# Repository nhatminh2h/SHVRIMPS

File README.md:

# SHVRIMPS: Synchronised High-Voltage aRbItrary Modular Power Supply

SHVRIMPS is a high-voltage generator and optical imaging setup, capable of
- Outputting arbitrary high-voltage waveforms with an amplitude of 15 kV and a rise time less than 10 ms for load resistances below 8 MΩ.
- Eight independent synchronous and asynchronous 16-bit output channels.
- Monitoring the output high voltages and currents at adjustable sampling rate. Maximum rate of 9875 samples per second.
- Recording video of samples at a rate of 120 fps at 640x480 pixels.
- Displaying live video feed, control panel, and monitoring data on a GUI, accessible over Ethernet.

It consists of three main components: 1) an imaging system based on a Raspberry Pi 4B with a camera, producing a live video stream 2) a DAQ board compatible with either Arduino Nano 33 BLE or ESP32 DevKitC, and c) a multi-channel arbitrary waveform HV supply.

The repository is structured as follows:
- demonstration: videos and matlab figures
- diagrams: block diagrams of the entire setup and individual components
- hardware: KiCAD files showing the PCB design files
- setup: setup files
- software: source files for the Pi and DAQ board

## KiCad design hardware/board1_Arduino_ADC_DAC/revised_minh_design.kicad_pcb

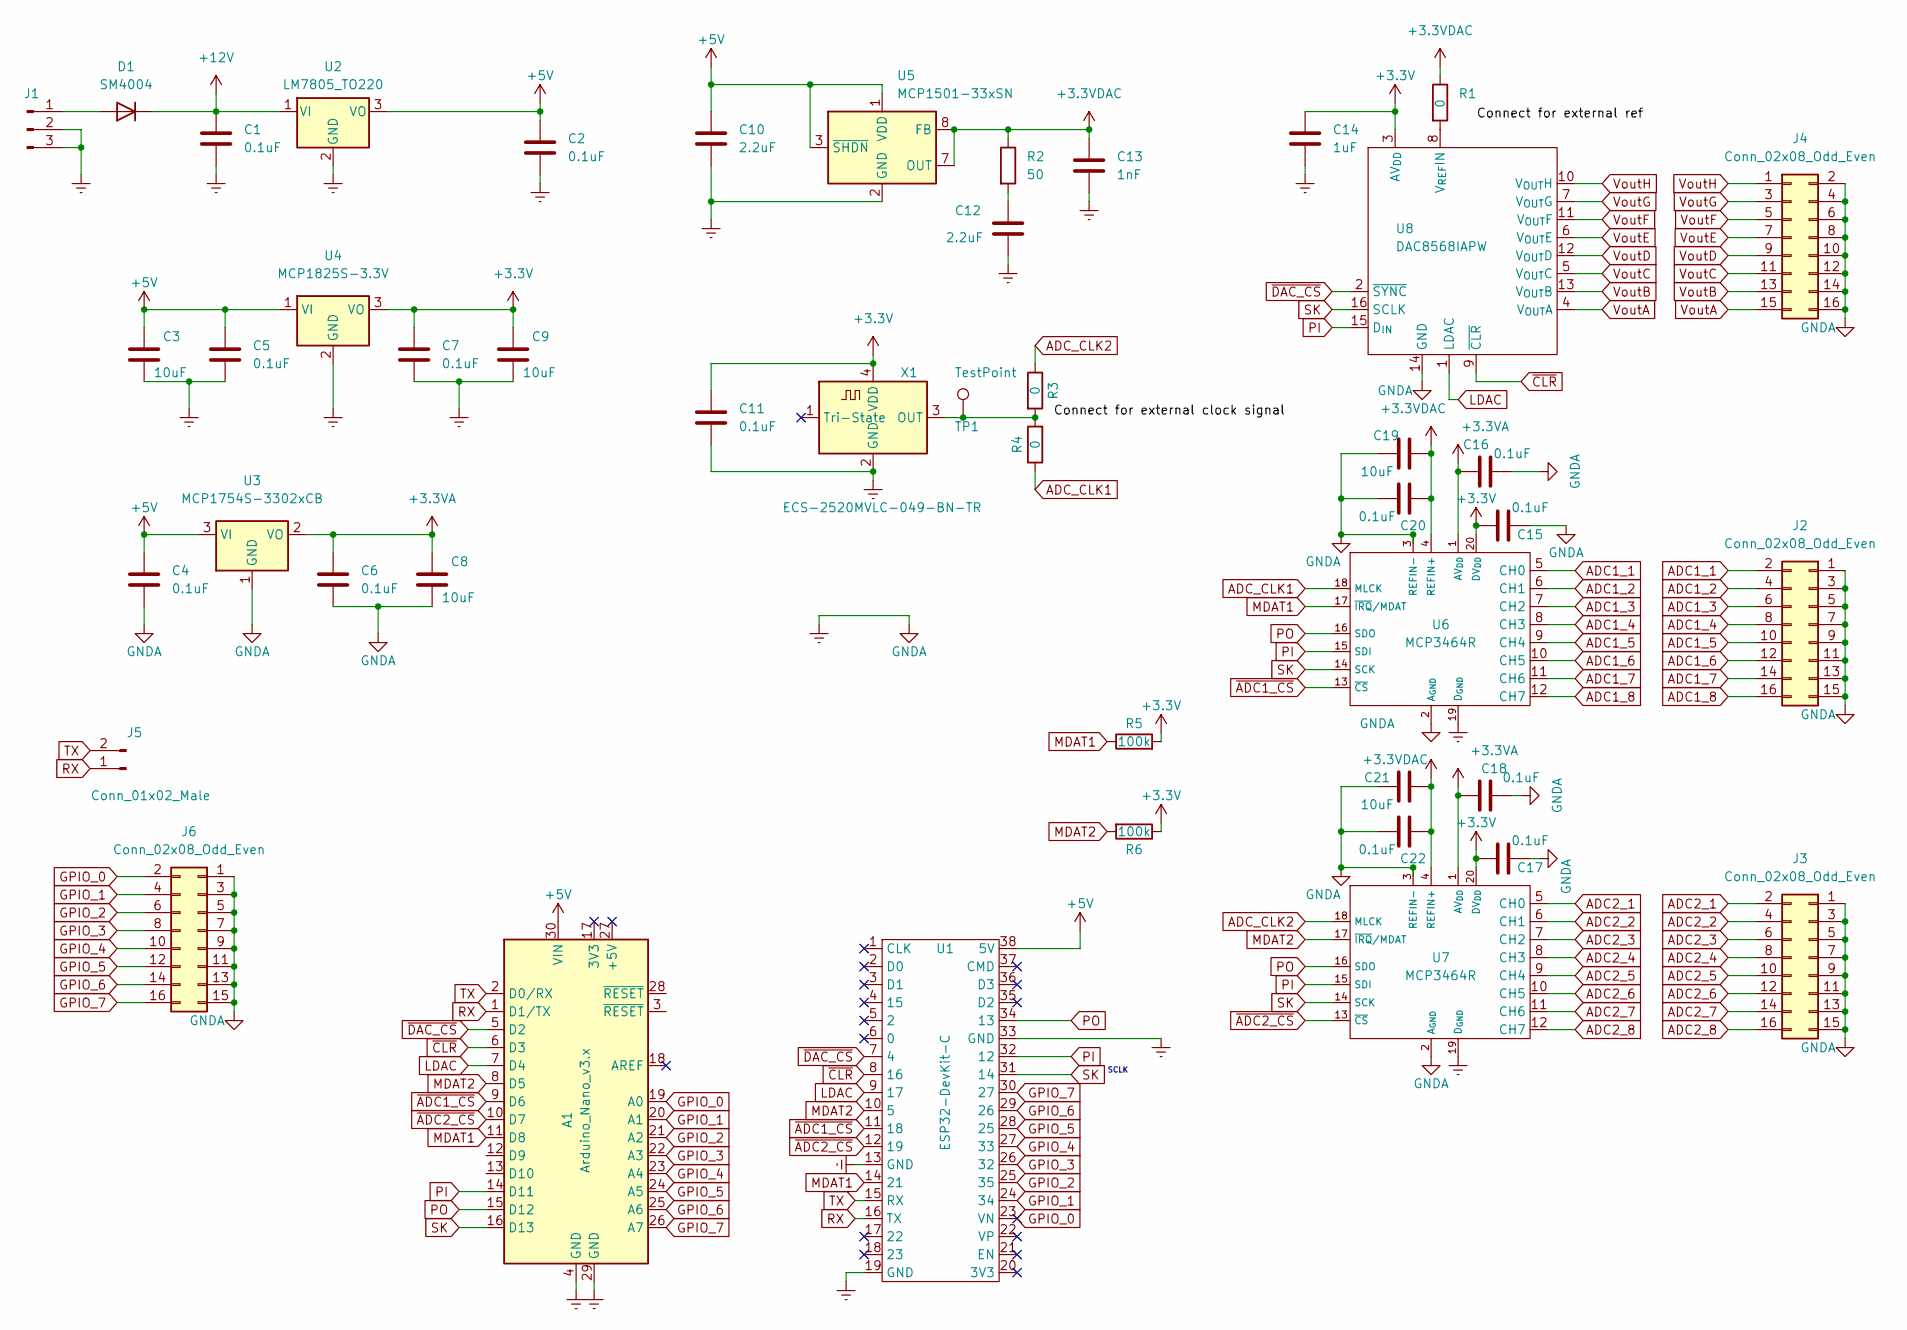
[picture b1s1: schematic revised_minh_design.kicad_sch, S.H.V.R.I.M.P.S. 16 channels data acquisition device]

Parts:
A1: Arduino_Nano_v3.x; Arduino_Nano
C1, C2, C4, C5, C6, C7, C11, C15, C16, C17, C18, C20, C22: 0.1uF; C_0805_2012Metric_Pad1.18x1.45mm_HandSolder
C3, C8, C9, C19, C21: 10uF; C_0805_2012Metric_Pad1.18x1.45mm_HandSolder
C10, C12: 2.2uF; C_0805_2012Metric_Pad1.18x1.45mm_HandSolder
C13: 1nF; C_0805_2012Metric_Pad1.18x1.45mm_HandSolder
C14: 1uF; C_0805_2012Metric_Pad1.18x1.45mm_HandSolder
D1: SM4004; D_MELF
J1: Conn_01x03_Male; PinSocket_1x03_P2.54mm_Vertical
J2, J3, J4, J6: Conn_02x08_Odd_Even; PinSocket_2x08_P2.54mm_Vertical
J5: Conn_01x02_Male; PinSocket_1x02_P2.54mm_Vertical
R1, R3, R4: 0; R_0805_2012Metric_Pad1.20x1.40mm_HandSolder
R2: 50; R_0805_2012Metric_Pad1.20x1.40mm_HandSolder
R5, R6: 100k; R_0805_2012Metric_Pad1.20x1.40mm_HandSolder
TP1: TestPoint; PinHeader_1x01_P2.54mm_Vertical
U1: ESP32-DevKit-C; ESP32-devkitC-v4
U2: LM7805_TO220; TO-220-3_Vertical
U3: MCP1754S-3302xCB; SOT-23
U4: MCP1825S-3.3V; SOT-223-3_TabPin2
U5: MCP1501-33xSN; SOIC-8_3.9x4.9mm_P1.27mm
U6, U7: MCP3464R; TSSOP-20_4.4x6.5mm_P0.65mm
U8: DAC8568IAPW; TSSOP-16-1EP_4.4x5mm_P0.65mm
X1: ECS-2520MVLC-049-BN-TR; Oscillator_SMD_ECS_2520MV-xxx-xx-4Pin_2.5x2.0mm

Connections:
+3.3VA: C6.1, C8.1, C16.1, C18.1, U3.2 (VO), U6.1 (AV_{DD}), U7.1 (AV_{DD})
+3.3VDAC: C13.1, C19.1, C20.1, C21.1, C22.1, R1.1, R2.1, U5.7 (OUT), U5.8 (FB), U6.4 (REFIN+), U7.4 (REFIN+)
+3V3: C7.1, C9.1, C11.1, C14.1, C15.1, C17.1, R5.2, R6.1, U4.3 (VO), U6.20 (DV_{DD}), U7.20 (DV_{DD}), U8.3 (AV_{DD}), X1.4 (VDD)
+5V: A1.30 (VIN), C2.1, C3.1, C4.1, C5.1, C10.1, U1.38 (5V), U2.3 (VO), U3.3 (VI), U4.1 (VI), U5.1 (VDD), U5.3 (~SHDN)
+12V: C1.1, D1.1 (K), U2.1 (VI)
ADC1_1: J2.2, U6.5 (CH0)
ADC1_2: J2.4, U6.6 (CH1)
ADC1_3: J2.6, U6.7 (CH2)
ADC1_4: J2.8, U6.8 (CH3)
ADC1_5: J2.10, U6.9 (CH4)
ADC1_6: J2.12, U6.10 (CH5)
ADC1_7: J2.14, U6.11 (CH6)
ADC1_8: J2.16, U6.12 (CH7)
ADC2_1: J3.2, U7.5 (CH0)
ADC2_2: J3.4, U7.6 (CH1)
ADC2_3: J3.6, U7.7 (CH2)
ADC2_4: J3.8, U7.8 (CH3)
ADC2_5: J3.10, U7.9 (CH4)
ADC2_6: J3.12, U7.10 (CH5)
ADC2_7: J3.14, U7.11 (CH6)
ADC2_8: J3.16, U7.12 (CH7)
ADC_CLK1: R4.1, U6.18 (MLCK)
ADC_CLK2: R3.1, U7.18 (MLCK)
Earth: A1.4 (GND), A1.29 (GND), C1.2, C2.2, C3.2, C4.2, C5.2, C6.2, C7.2, C8.2, C9.2, C10.2, C11.2, C12.2, C13.2, C14.2, C15.2, C16.2, C17.2, C18.2, C19.2, C20.2, C21.2, C22.2, J1.2, J1.3, J2.1, J2.3, J2.5, J2.7, J2.9, J2.11, J2.13, J2.15, J3.1, J3.3, J3.5, J3.7, J3.9, J3.11, J3.13, J3.15, J4.2, J4.4, J4.6, J4.8, J4.10, J4.12, J4.14, J4.16, J6.1, J6.3, J6.5, J6.7, J6.9, J6.11, J6.13, J6.15, U1.13 (GND), U1.19 (GND), U1.33 (GND), U2.2 (GND), U3.1 (GND), U4.2 (GND), U5.2 (GND), U5.4 (GND), U5.5 (GND), U5.6 (GND), U6.2 (A_{GND}), U6.3 (REFIN-), U6.19 (D_{GND}), U7.2 (A_{GND}), U7.3 (REFIN-), U7.19 (D_{GND}), U8.14 (GND), X1.2 (GND)
GPIO_0: A1.19 (A0), J6.2, U1.23 (VN)
GPIO_1: A1.20 (A1), J6.4, U1.24 (34)
GPIO_2: A1.21 (A2), J6.6, U1.25 (35)
GPIO_3: A1.22 (A3), J6.8, U1.26 (32)
GPIO_4: A1.23 (A4), J6.10, U1.27 (33)
GPIO_5: A1.24 (A5), J6.12, U1.28 (25)
GPIO_6: A1.25 (A6), J6.14, U1.29 (26)
GPIO_7: A1.26 (A7), J6.16, U1.30 (27)
LDAC: A1.7 (D4), U1.9 (17), U8.1 (LDAC)
MDAT1: A1.11 (D8), R5.1, U1.14 (21), U6.17 (~IRQ/MDAT)
MDAT2: A1.8 (D5), R6.2, U1.10 (5), U7.17 (~IRQ/MDAT)
unnamed: C12.1, R2.2
unnamed: D1.2 (A), J1.1
unnamed: R1.2, U8.8 (V_{REF}IN)
unnamed: R3.2, R4.2, TP1.1, X1.3 (OUT)
PI: A1.14 (D11), U1.32 (12), U6.15 (SDI), U7.15 (SDI), U8.15 (D_{IN})
PO: A1.15 (D12), U1.34 (13), U6.16 (SDO), U7.16 (SDO)
RX: A1.1 (D1/TX), J5.1, U1.16 (TX)
SK: A1.16 (D13), U1.31 (14), U6.14 (SCK), U7.14 (SCK), U8.16 (SCLK)
TX: A1.2 (D0/RX), J5.2, U1.15 (RX)
VoutA: J4.15, U8.4 (V_{OUT}A)
VoutB: J4.13, U8.13 (V_{OUT}B)
VoutC: J4.11, U8.5 (V_{OUT}C)
VoutD: J4.9, U8.12 (V_{OUT}D)
VoutE: J4.7, U8.6 (V_{OUT}E)
VoutF: J4.5, U8.11 (V_{OUT}F)
VoutG: J4.3, U8.7 (V_{OUT}G)
VoutH: J4.1, U8.10 (V_{OUT}H)
~ADC1_CS: A1.9 (D6), U1.11 (18), U6.13 (~CS)
~ADC2_CS: A1.10 (D7), U1.12 (19), U7.13 (~CS)
~CLR: A1.6 (D3), U1.8 (16), U8.9 (~CLR)
~DAC_CS: A1.5 (D2), U1.7 (4), U8.2 (~SYNC)

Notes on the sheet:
SCLK

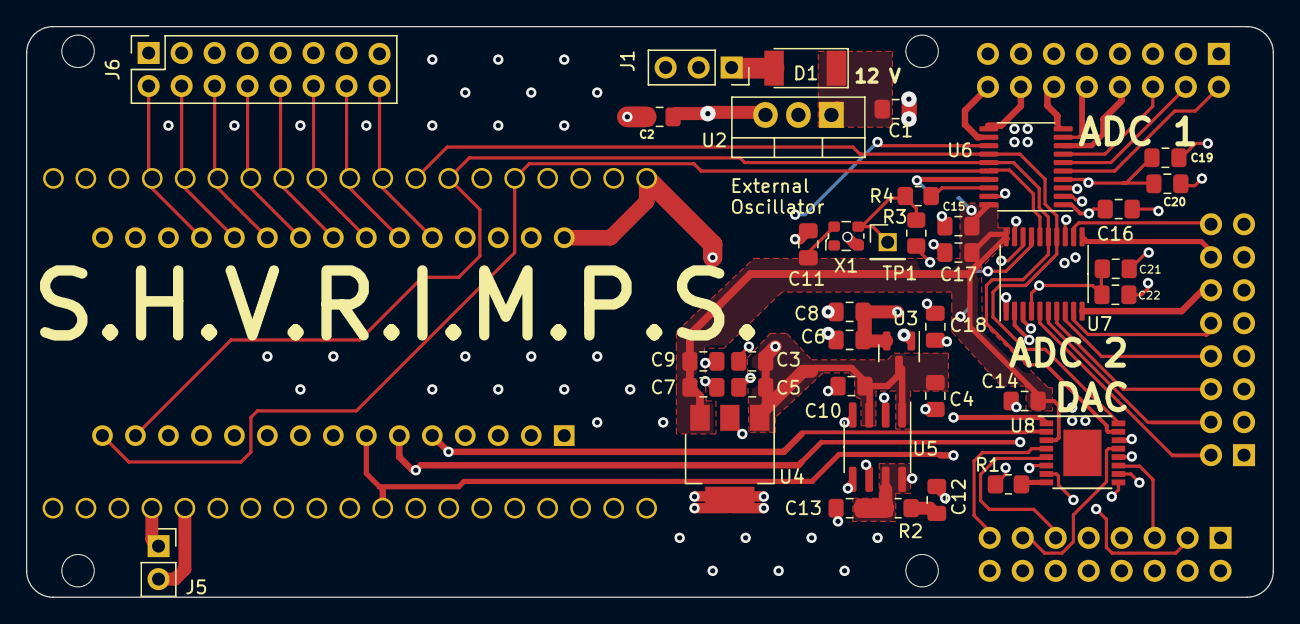
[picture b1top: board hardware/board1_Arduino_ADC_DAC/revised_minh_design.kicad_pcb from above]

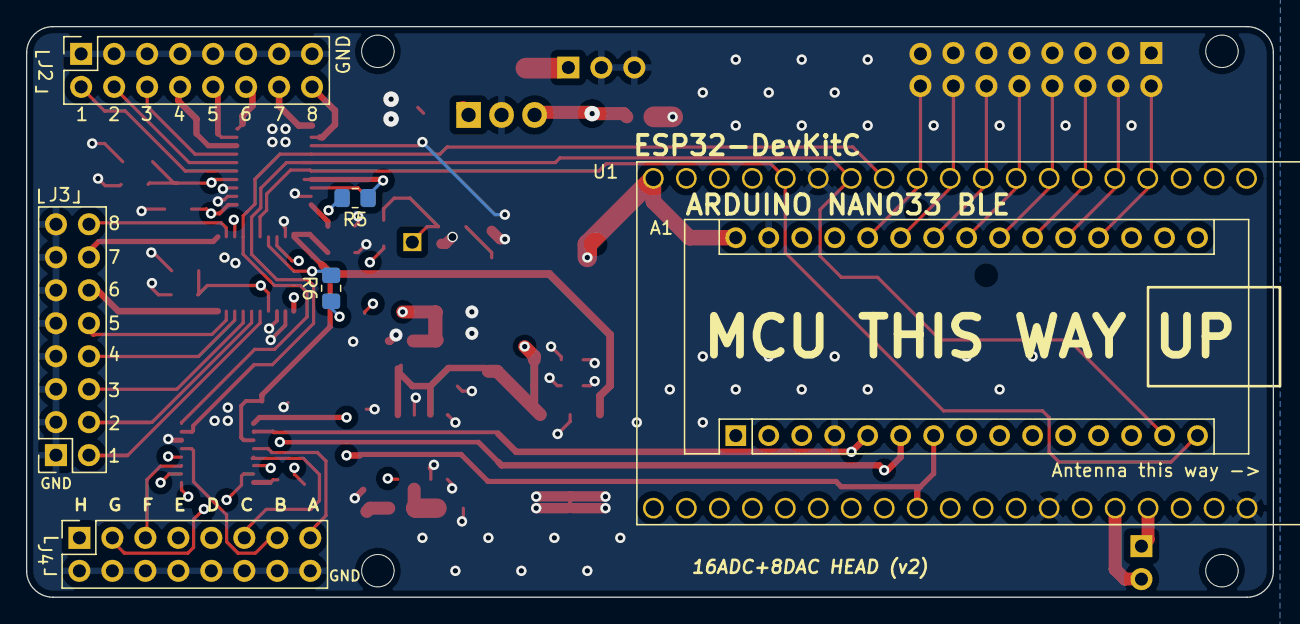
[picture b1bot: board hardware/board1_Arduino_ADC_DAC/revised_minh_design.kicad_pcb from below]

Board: 4 copper layers, 96.0 x 43.9 mm, 50 parts (7 on the bottom side), 56 nets.

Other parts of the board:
 : MountingHole_2.5mm
 #2,  #3,  #4: MountingHole_2.5mm

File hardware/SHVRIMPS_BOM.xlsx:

Ref | Qnty | Value | Description | Vendor | Manufacture number | Alternative Option | Unit Price | Total Price
A1, | 1 | Arduino_Nano_v3.x | Arduino Nano 33 BLE | https://uk.rs-online.com/web/p/arduino/1927587 | ABX00030 |  | 25.86 | 25.86
C1, C2, C4, C5, C6, C7, C11, C15, C16, C17, C18, C20, C22, | 13 | 0.1uF | Capacitor_SMD_0805 | https://www.mouser.co.uk/ProductDetail/Vishay-Vitramon/VJ080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 | VJ0805Y104JXAMR | SMD components of same value | 0.34399999999999997 | 4.4719999999999995
C3, C8, C9, C19, C21, | 5 | 10uF | Capacitor_SMD_0806 | https://www.mouser.co.uk/ProductDetail/KYOCERA-AVX/0805ZD106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 | 0805ZD106KAT2A | SMD components of same value | 0.17599999999999999 | 0.87999999999999989
C10, C12, | 2 | 2.2uF | Capacitor_SMD_0807 | https://www.mouser.co.uk/ProductDetail/KEMET/C0805C225K3RACA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 |  | SMD components of same value | 0.24399999999999999 | 0.48799999999999999
C13, | 1 | 1nF | Capacitor_SMD_0808 | https://www.mouser.co.uk/ProductDetail/KYOCERA-AVX/08055A102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 |  | SMD components of same value | 0.109 | 0.109
C14, | 1 | 1uF | Capacitor_SMD_0809 | https://www.mouser.co.uk/ProductDetail/KYOCERA-AVX/0805DC105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 |  | SMD components of same value | 0.185 | 0.185
D1, | 1 | SM4004 | 400V 1A General Purpose Rectifier Diode, MELF | https://eu.mouser.com/ProductDetail/Rectron/FM4004-W?qs=Iw9U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 | FM4004-W | SMD components of same value | 0.254 | 0.254
J1, | 1 | Conn_01x03_Male | Single row, 01x03, 2.54mm pitch | https://www.mouser.co.uk/ProductDetail/Molex/90136-1303?qs=k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 | 90136-1303 | 2.54mm pitch connectors | 1.45 | 1.45
 | 1 | Conn_01x03_Female | Receptacle | https://www.mouser.co.uk/ProductDetail/Molex/90156-0143?qs=j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 | 90156-0143 | 2.54mm pitch connectors | 0.53800000000000003 | 0.53800000000000003
J2, J3, J4, | 3 | Conn_02x08_Male | Double row, 02x08, 2.54mm pitch | https://www.mouser.co.uk/ProductDetail/Molex/90130-1316?qs=p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 | 90130-1316 | 2.54mm pitch connectors | 4.29 | 12.870000000000001
 | 3 | Conn_02x08_Female |  | https://www.mouser.co.uk/ProductDetail/Molex/90142-0016?qs=k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 | 90142-0016 | 2.54mm pitch connectors | 1.24 | 3.7199999999999998
J5, | 1 | Conn_01x02_Male | Single row, 01x02, 2.54mm pitch | https://www.mouser.co.uk/ProductDetail/Molex/90136-1202?qs=z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 | 90136-1202 | 2.54mm pitch connectors | 1.1399999999999999 | 1.1399999999999999
 | 1 | Conn_01x02_Female |  | https://www.mouser.co.uk/ProductDetail/Molex/90156-0142?qs=j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 | 90156-0142 | 2.54mm pitch connectors | 0.38600000000000001 | 0.38600000000000001
R1, R3, R4, | 3 | 0 Ohm | Resistor_SMD_0803 | https://www.mouser.co.uk/ProductDetail/Vishay-Dale/CRCW08050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 | CRCW08050000Z0EAC | SMD components of same value | 8.4000000000000005E-2 | 0.252
R2, | 1 | 50 Ohm | Resistor_SMD_0804 | https://uk.farnell.com/panasonic/era6aeb49r9v/res-0805-49r9-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 | ERA6AEB49R9V | SMD components of same value | 0.253 | 0.253
R5, R6, | 2 | 100k Ohm | Resistor_SMD_0805 | https://www.mouser.co.uk/ProductDetail/Vishay-Dale/RCS080510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 |  | SMD components of same value | 0.20200000000000001 | 0.40400000000000003
U1, | 1 | ESP32-DevKit-C | Alternative microcontroller: ESP32-devkitC-v4 |  |  |  |  | 0
U2, | 1 | LM7805_TO220 | Positive 1A 35V Linear Regulator, Fixed Output 5V, TO-220-3 | https://uk.farnell.com/stmicroelectronics/l7805abv/ic-v-reg-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 | L7805ABV |  | 0.72099999999999997 | 0.72099999999999997
U3, | 1 | MCP1754S-3302xCB | Fixed 150mA Low Dropout Voltage Regulator, Positive, 3.3V output, SOT-23 | https://uk.rs-online.com/web/p/voltage-regulators/7559521 | MCP1754ST-3302E/CB | LDO with the same specification and footprint(make note of the pin out as diffe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 | 0.44600000000000001 | 0.44600000000000001
U4, | 1 | MCP1825S-3.3V | 500mA, Low-Voltage, Low Quiescent Current LDO Regulator, SOT-223-3 | https://www.mouser.co.uk/ProductDetail/Microchip-Technology-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 | MCP1825ST-3302E/DB | LDO with the same specification and footprint(make note of the pin out as diffe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 | 0.57999999999999996 | 0.57999999999999996
U5, | 1 | MCP1501-33xSN | 3.3V, 0.1%, 20mA, Precision Voltage Reference, SOIC-8 | https://uk.farnell.com/microchip/mcp1501-30e-sn/voltage-ref-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 | MCP1501-30E/SN | LDO with the same specification and footprint(make note of the pin out as diffe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 | 1.2875000000000001 | 1.2875000000000001
U6, U7, | 2 | MCP3464R | TSSOP-20_4.4x6.5mm_P0.65mm | https://www.mouser.co.uk/ProductDetail/Microchip-Technology/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 | MCP3464R-E/ST | MCP3x6x family | 4.38 | 8.76
U8, | 1 | DAC8568IAPW | TSSOP-16- | https://www.mouser.co.uk/ProductDetail/Texas-Instruments/DAC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 | DAC8568IAPW | DAC856x family | 21.65 | 21.65
X1, | 1 | ECS-2520MVLC-049-BN-TR | HCMOS Crystal Clock Oscillator, 2.5x2.0 mm SMD | https://www.mouser.co.uk/ProductDetail/ECS/ECS-2520MVLC-049-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 | ECS-2520MVLC-049-BN-TR | Oscillator with frequency under 20 MHz and similar footprint. | 1.17 | 1.17
 | 1 | PCB | 4-Layer PCB | JLC-PCB |  |  | 1.3080000000000001 | 1.3080000000000001
 | 1 | PCB Stencil | Thin sheet of metal masking for solder paste application | JLC-PCB |  |  | 10
 |  |  |  |  |  |  | Total | 89.183500000000009

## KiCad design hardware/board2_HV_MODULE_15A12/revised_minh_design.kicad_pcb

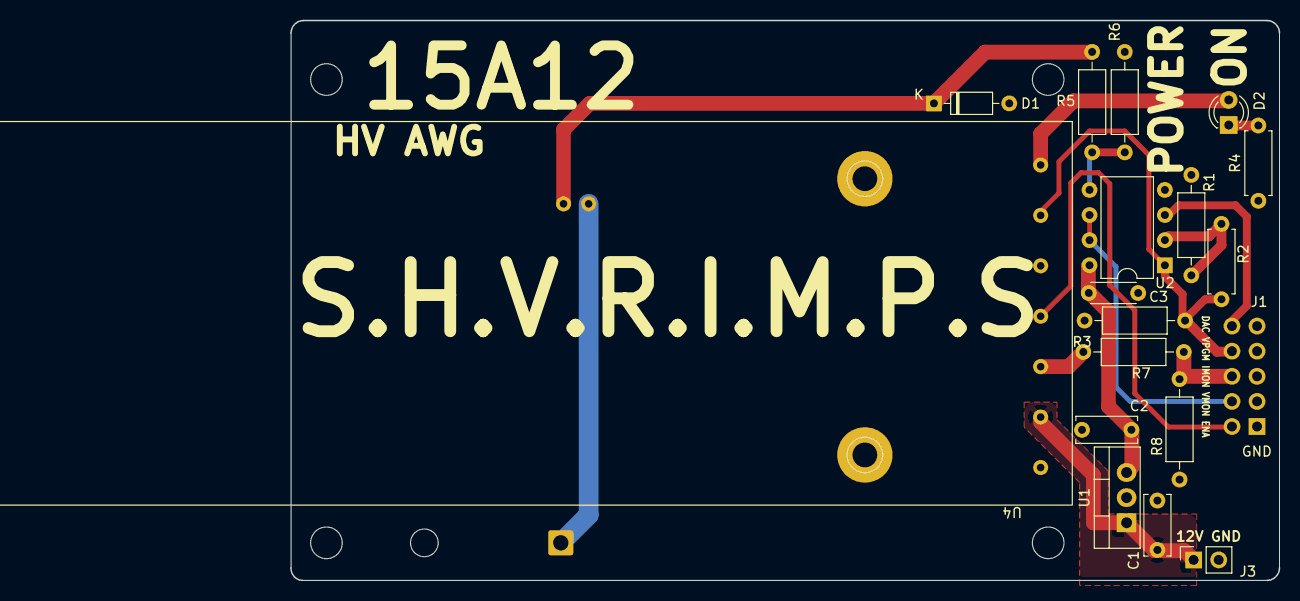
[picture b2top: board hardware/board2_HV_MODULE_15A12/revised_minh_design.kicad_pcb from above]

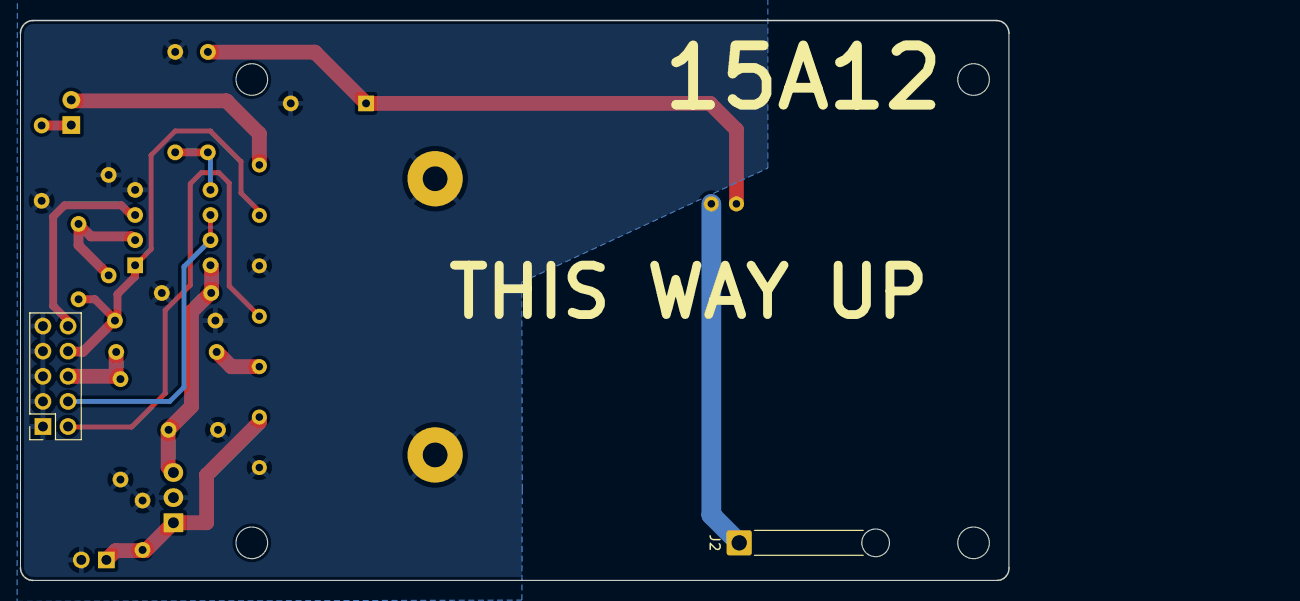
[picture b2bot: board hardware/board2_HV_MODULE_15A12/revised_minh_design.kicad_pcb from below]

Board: 2 copper layers, 100.0 x 56.6 mm, 25 parts (2 on the bottom side), 15 nets.

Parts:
 : MountingHole_3.2mm_M3
 #2,  #4,  #6: MountingHole_3.2mm_M3
 #3: MountingHole_3.2mm_M3_DIN965_Pad
 #5: (no value)
C1, C2: 0.1uF; C_Disc_D6.0mm_W2.5mm_P5.00mm
C3: 0.1uF; C_Disc_D4.3mm_W1.9mm_P5.00mm
D1: TZX3V6A-TR; D_DO-35_SOD27_P7.62mm_Horizontal
D2: LED; LED_D3.0mm_Clear
J1: Conn_01x07_Male; PinSocket_2x05_P2.54mm_Vertical
J2: Conn_01x01_Male; SolderWire-0.75sqmm_1x01_D1.25mm_OD2.3mm_Relief
J3: Conn_01x02_Male; PinSocket_1x02_P2.54mm_Vertical
R1: 4.7k; R_Axial_DIN0207_L6.3mm_D2.5mm_P10.16mm_Horizontal
R2: 2k; R_Axial_DIN0207_L6.3mm_D2.5mm_P7.62mm_Horizontal
R3: 10k; R_Axial_DIN0207_L6.3mm_D2.5mm_P10.16mm_Horizontal
R4: 2.2k; R_Axial_DIN0207_L6.3mm_D2.5mm_P7.62mm_Horizontal
R5, R7: 3k9; R_Axial_DIN0207_L6.3mm_D2.5mm_P10.16mm_Horizontal
R6, R8: 1k1; R_Axial_DIN0207_L6.3mm_D2.5mm_P10.16mm_Horizontal
U1: LM7805_TO220; TO-220-3_Vertical
U2: NE5532; DIP-8_W7.62mm
U4: 15A12; Advanced Energy 15A12P4

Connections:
+5V: C2.1, C3.1, U1.3 (VO), U2.8 (V+)
+12V: C1.1, J3.1, U1.1 (VI), U4.2 (DC_INPUT_POWER)
DAC_SIG: J1.10, U2.3 (+)
ENABLE: J1.2, U4.4 (HV_ENABLE)
IMON: R7.2, U4.3 (Imon)
IMON_3V3: J1.6, R7.1, R8.2
unnamed: D2.1 (K), R4.2
unnamed: D2.2 (A), U4.7 (5VDC_REF)
unnamed: J2.1, U4.2-1 (HV_RTN)
unnamed: R1.1, R2.1, U2.2 (-)
SGND: #3.1, #5.1, C1.2, C2.2, C3.2, D1.2 (A), J1.1, J1.3, J1.5, J1.7, J1.9, J3.2, R1.2, R3.2, R4.1, R6.1, R8.1, U1.2 (GND), U2.4 (V-), U4.1 (DC_INPUT_POWER_GROUND), U4.5 (SIGNAL_GROUND_RET)
VMON: D1.1 (K), R5.2, U4.2-2 (Vmon)
VMON_3V3: J1.4, U2.6 (-), U2.7
VMON_OPAMP: R5.1, R6.2, U2.5 (+)
VPGM: J1.8, R2.2, R3.1, U2.1, U4.6 (Vprog)

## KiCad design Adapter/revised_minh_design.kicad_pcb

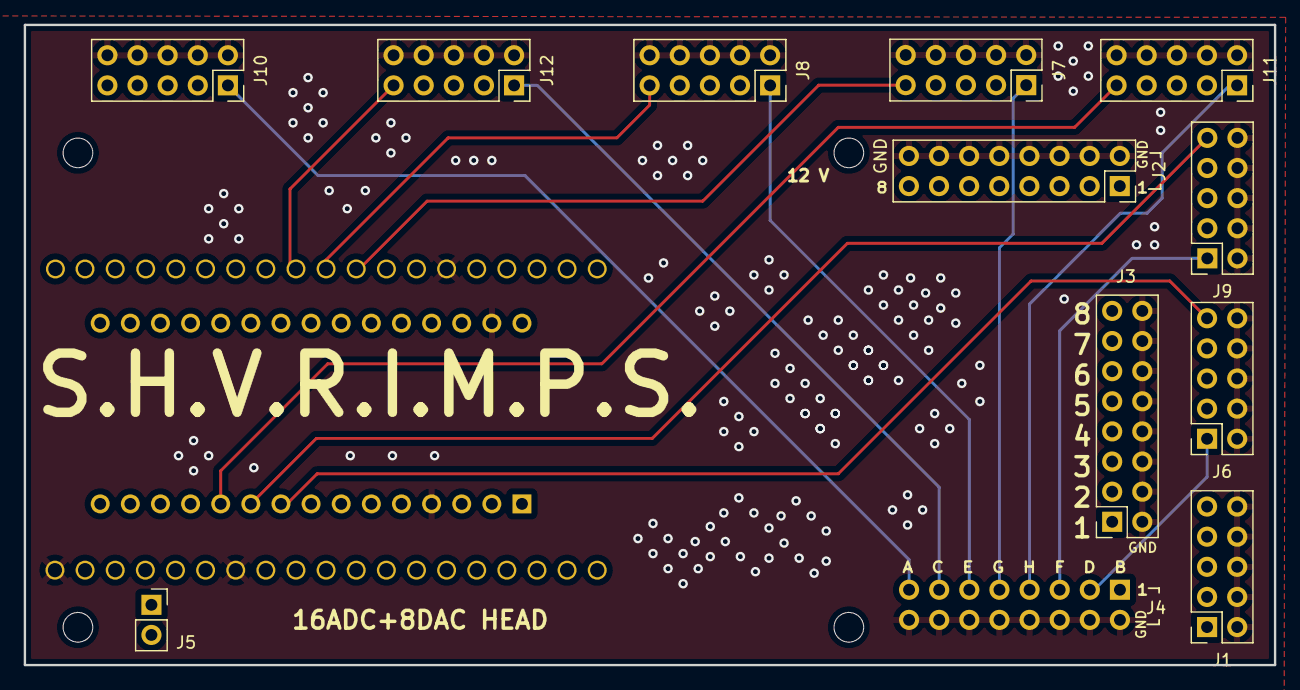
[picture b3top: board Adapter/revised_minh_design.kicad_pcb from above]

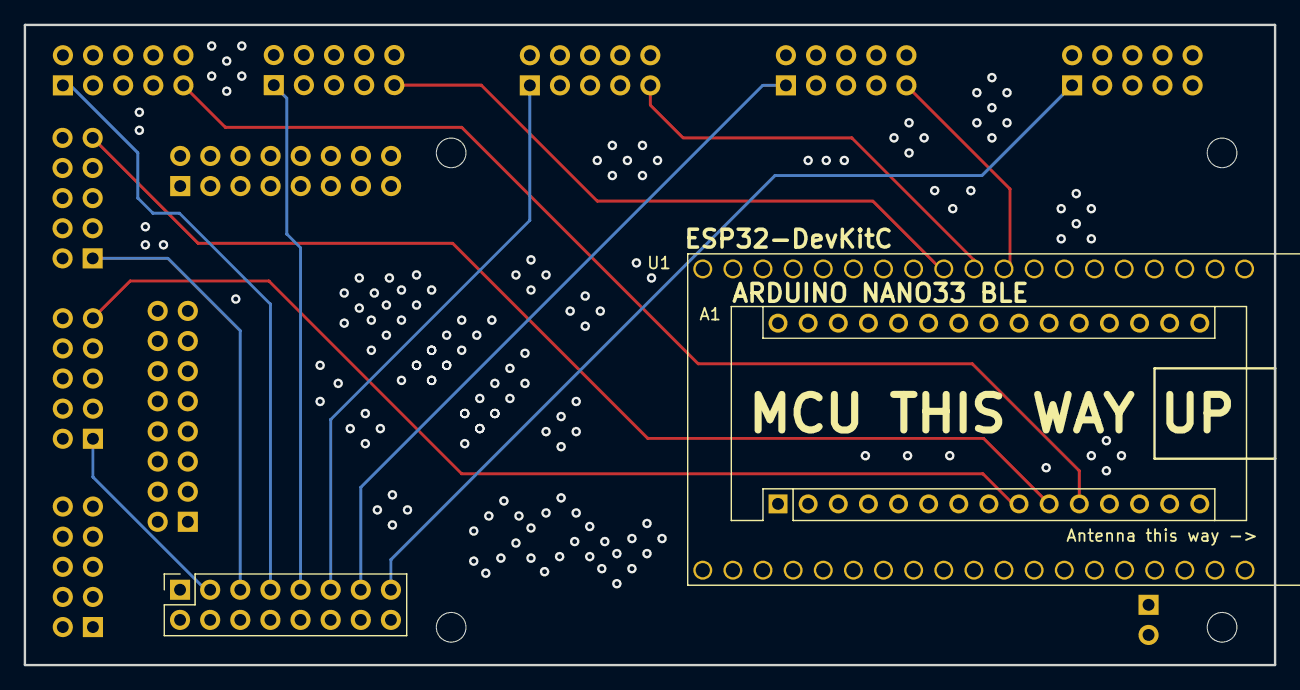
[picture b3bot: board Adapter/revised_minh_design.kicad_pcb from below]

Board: 4 copper layers, 105.4 x 54.0 mm, 18 parts (3 on the bottom side), 33 nets.

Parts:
 : MountingHole_2.5mm
 #2,  #3,  #4: MountingHole_2.5mm
A1: Arduino_Nano_v3.x; Arduino_Nano
J1, J6, J7, J8, J9, J10, J11, J12: Conn_02x05_Odd_Even; PinSocket_2x05_P2.54mm_Vertical
J2, J3, J4: Conn_02x08_Odd_Even; PinSocket_2x08_P2.54mm_Vertical
J5: Conn_01x02_Male; PinSocket_1x02_P2.54mm_Vertical
U1: ESP32-DevKit-C; ESP32-devkitC-v4

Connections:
ADC1_1: J2.1, J7.5
ADC1_2: J2.3, J7.7
ADC1_3: J2.5, J8.5
ADC1_4: J2.7, J8.7
ADC1_5: J2.9, J10.5
ADC1_6: J2.11, J10.7
ADC1_7: J2.13, J12.5
ADC1_8: J2.15, J12.7
ADC2_1: J1.5, J3.1
ADC2_2: J1.7, J3.3
ADC2_3: J3.5, J6.5
ADC2_4: J3.7, J6.7
ADC2_5: J3.9, J9.5
ADC2_6: J3.11, J9.7
ADC2_7: J3.13, J11.5
ADC2_8: J3.15, J11.7
ENA1: A1.22 (A3), J10.9, U1.24 (34)
ENA2: A1.23 (A4), J12.9, U1.28 (25)
ENA3: A1.24 (A5), J8.9, U1.29 (26)
ENA4: A1.25 (A6), J7.9, U1.30 (27)
ENA5: A1.11 (D8), J11.9
ENA6: A1.10 (D7), J9.9
ENA7: A1.9 (D6), J6.9, U1.5 (2)
ENA8: A1.8 (D5), J1.9, U1.4 (15)
Earth: A1.4 (GND), A1.29 (GND), J1.2, J1.4, J1.6, J1.8, J1.10, J2.2, J2.4, J2.6, J2.8, J2.10, J2.12, J2.14, J2.16, J3.2, J3.4, J3.6, J3.8, J3.10, J3.12, J3.14, J3.16, J4.2, J4.4, J4.6, J4.8, J4.10, J4.12, J4.14, J4.16, J6.2, J6.4, J6.6, J6.8, J6.10, J7.2, J7.4, J7.6, J7.8, J7.10, J8.2, J8.4, J8.6, J8.8, J8.10, J9.2, J9.4, J9.6, J9.8, J9.10, J10.2, J10.4, J10.6, J10.8, J10.10, J11.2, J11.4, J11.6, J11.8, J11.10, J12.2, J12.4, J12.6, J12.8, J12.10, U1.13 (GND), U1.19 (GND), U1.33 (GND)
VoutA: J4.15, J10.1
VoutB: J1.1, J4.1
VoutC: J4.13, J12.1
VoutD: J4.3, J6.1
VoutE: J4.11, J8.1
VoutF: J4.5, J9.1
VoutG: J4.9, J7.1
VoutH: J4.7, J11.1

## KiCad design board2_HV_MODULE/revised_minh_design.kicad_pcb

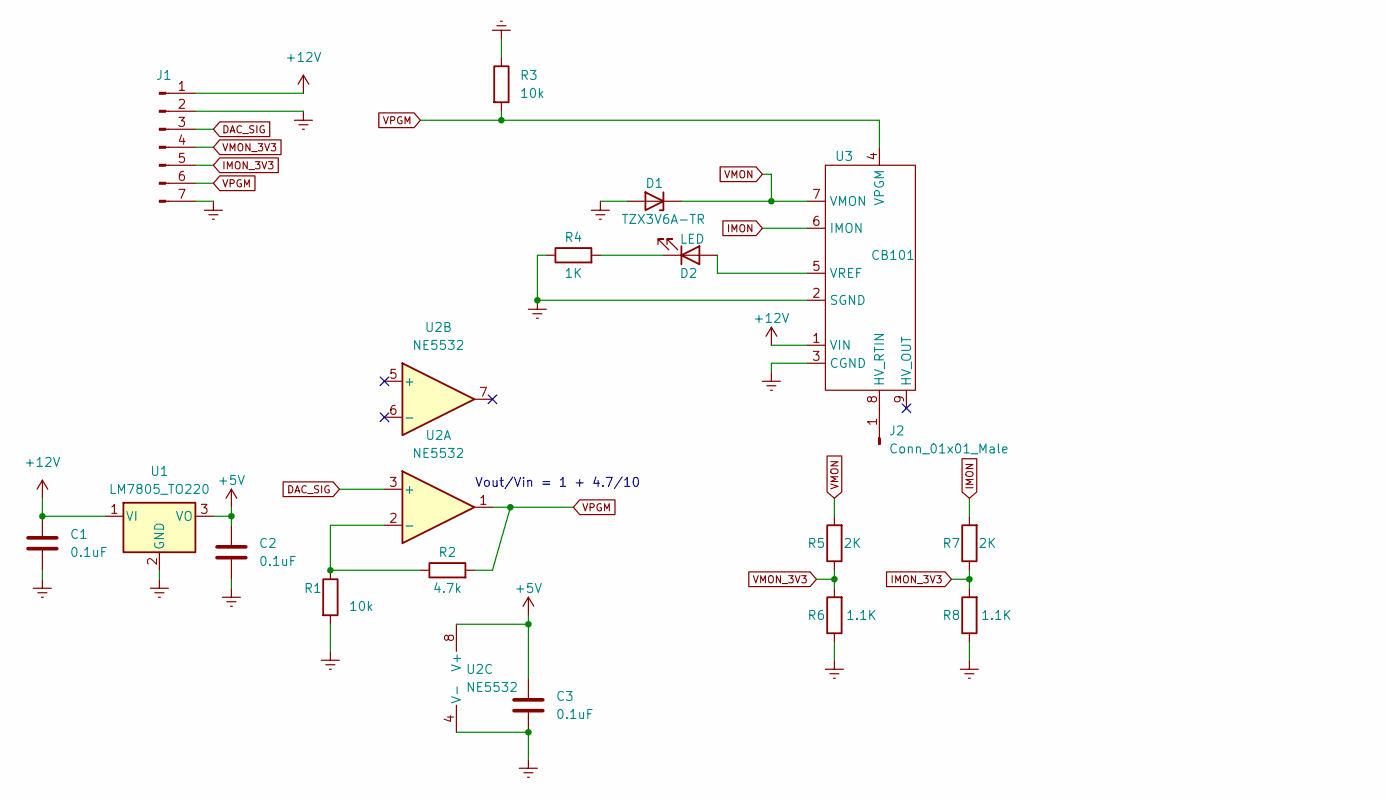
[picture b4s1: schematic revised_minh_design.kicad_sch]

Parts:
C1, C2, C3: 0.1uF; C_Disc_D6.0mm_W2.5mm_P5.00mm
D1: TZX3V6A-TR; D_DO-35_SOD27_P7.62mm_Horizontal
D2: LED; LED_D3.0mm_Clear
J1: Conn_01x07_Male; PinSocket_1x07_P2.54mm_Vertical
J2: Conn_01x01_Male; SolderWire-0.75sqmm_1x01_D1.25mm_OD2.3mm_Relief
R1, R3: 10k; R_Axial_DIN0207_L6.3mm_D2.5mm_P10.16mm_Horizontal
R2: 4.7k; R_Axial_DIN0207_L6.3mm_D2.5mm_P7.62mm_Horizontal
R4: 1K; R_Axial_DIN0207_L6.3mm_D2.5mm_P10.16mm_Horizontal
R5: 2K; R_Axial_DIN0207_L6.3mm_D2.5mm_P15.24mm_Horizontal
R6, R8: 1.1K; R_Axial_DIN0207_L6.3mm_D2.5mm_P10.16mm_Horizontal
R7: 2K; R_Axial_DIN0207_L6.3mm_D2.5mm_P10.16mm_Horizontal
U1: LM7805_TO220; TO-220-3_Vertical
U2: NE5532; DIP-8_W7.62mm
U3: CB101

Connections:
+5V: C2.1, C3.1, U1.3 (VO), U2.8 (V+)
+12V: C1.1, J1.1, U1.1 (VI), U3.1 (VIN)
DAC_SIG: J1.3, U2.3 (+)
Earth: C1.2, C2.2, C3.2, D1.2 (A), J1.2, J1.7, R1.2, R3.1, R4.1, R6.1, R8.1, U1.2 (GND), U2.4 (V-), U3.2 (SGND), U3.3 (CGND)
IMON: R7.2, U3.6 (IMON)
IMON_3V3: J1.5, R7.1, R8.2
unnamed: D2.1 (K), R4.2
unnamed: D2.2 (A), U3.5 (VREF)
unnamed: J2.1, U3.8 (HV_RTIN)
unnamed: R1.1, R2.1, U2.2 (-)
VMON: D1.1 (K), R5.2, U3.7 (VMON)
VMON_3V3: J1.4, R5.1, R6.2
VPGM: J1.6, R2.2, R3.2, U2.1, U3.4 (VPGM)

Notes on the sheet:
Vout/Vin = 1 + 4.7/10

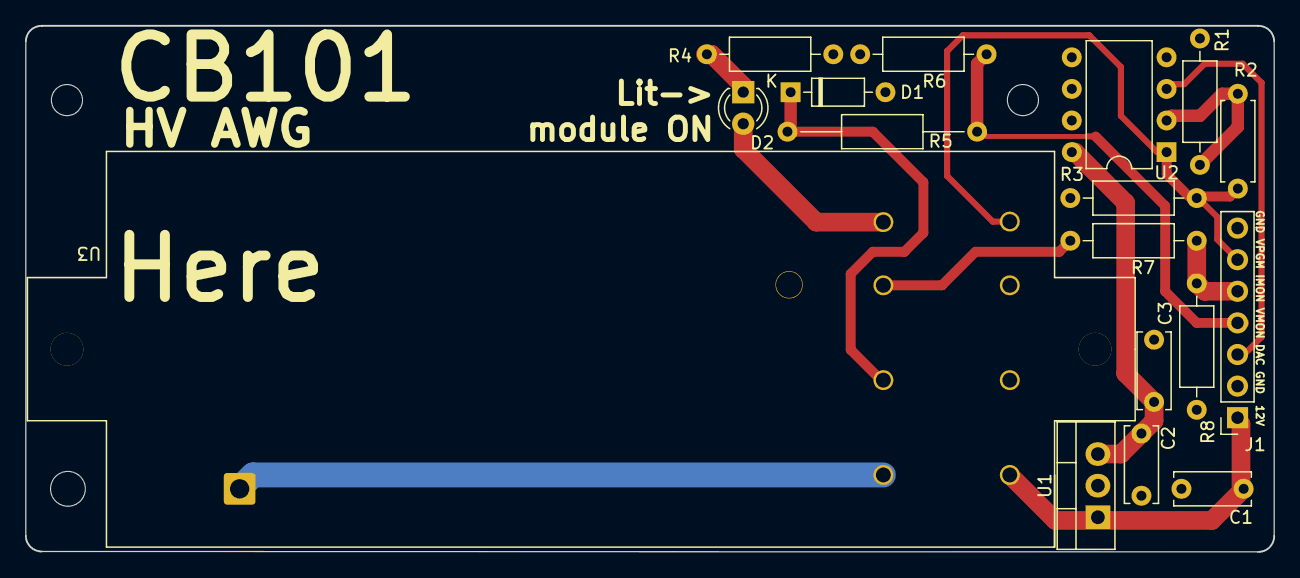
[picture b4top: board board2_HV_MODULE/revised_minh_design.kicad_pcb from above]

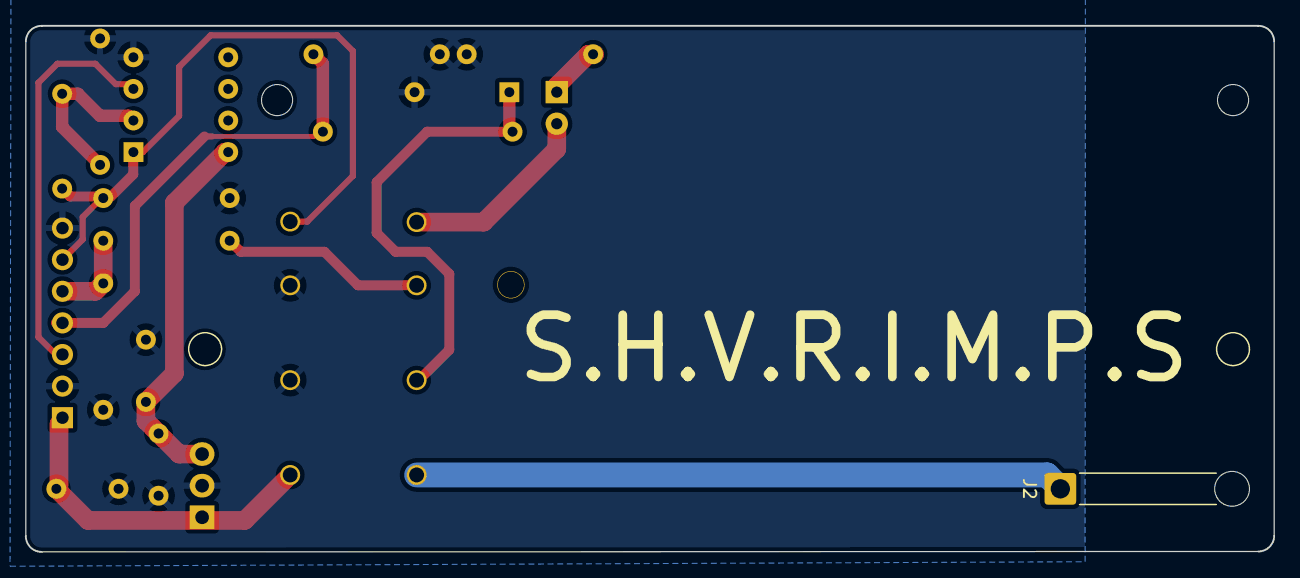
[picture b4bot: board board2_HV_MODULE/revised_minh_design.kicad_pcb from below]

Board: 2 copper layers, 100.3 x 42.3 mm, 20 parts (2 on the bottom side), 13 nets.

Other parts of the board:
 : MountingHole_2.5mm
 #2: MountingHole_2.5mm

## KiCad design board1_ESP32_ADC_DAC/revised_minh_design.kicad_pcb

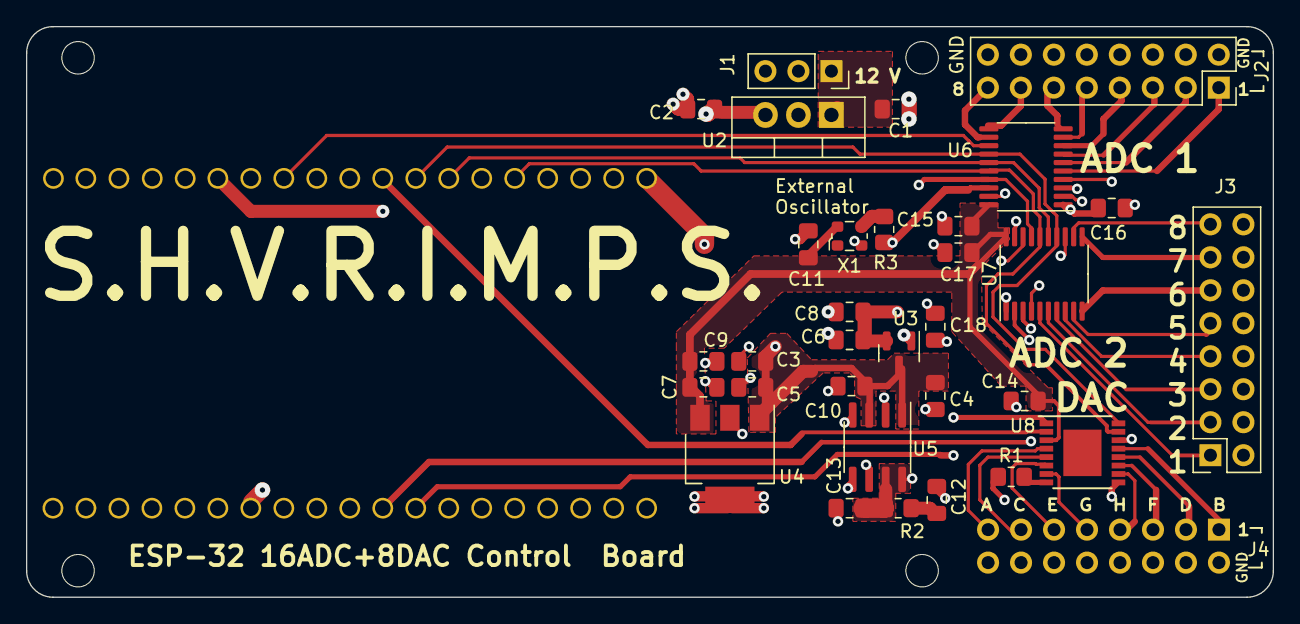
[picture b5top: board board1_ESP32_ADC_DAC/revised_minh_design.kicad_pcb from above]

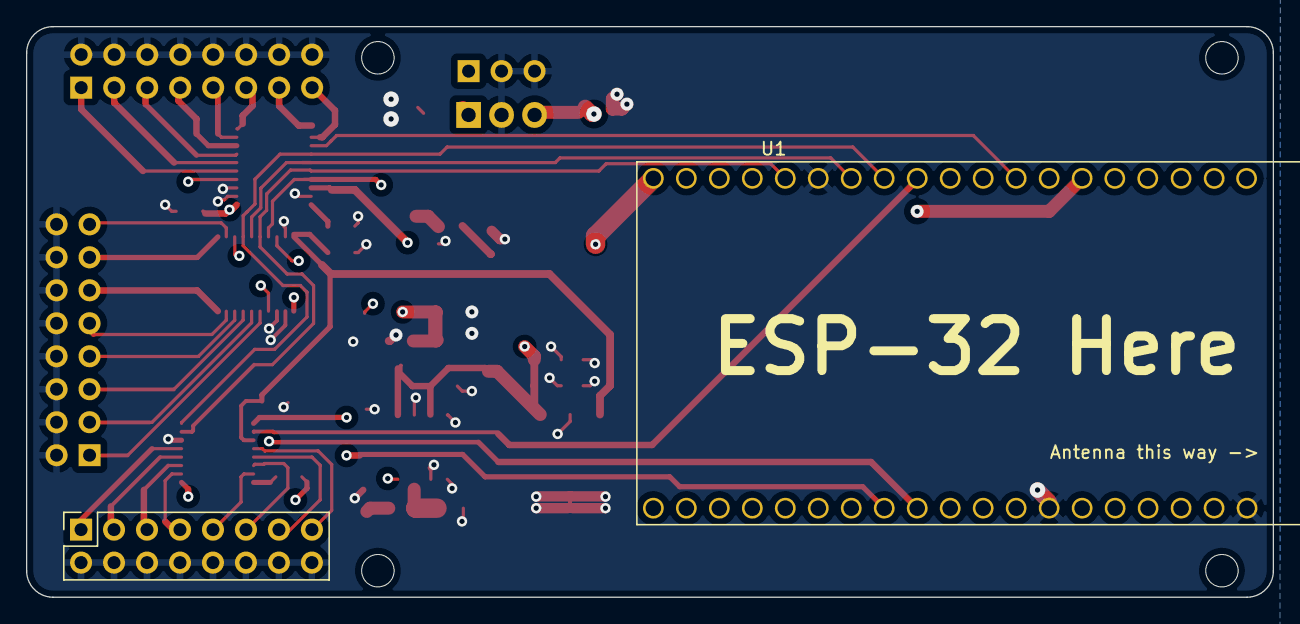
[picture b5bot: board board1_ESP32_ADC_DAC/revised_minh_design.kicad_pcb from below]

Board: 4 copper layers, 96.0 x 43.9 mm, 38 parts (2 on the bottom side), 43 nets.

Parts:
 : MountingHole_2.5mm
 #2,  #3,  #4: MountingHole_2.5mm
C1, C2, C4, C5, C6, C7, C11, C15, C16, C17, C18: 0.1uF; C_0805_2012Metric_Pad1.18x1.45mm_HandSolder
C3, C8, C9: 10uF; C_0805_2012Metric_Pad1.18x1.45mm_HandSolder
C10, C12: 2.2uF; C_0805_2012Metric_Pad1.18x1.45mm_HandSolder
C13: 1nF; C_0805_2012Metric_Pad1.18x1.45mm_HandSolder
C14: 1uF; C_0805_2012Metric_Pad1.18x1.45mm_HandSolder
J1: Conn_01x03_Male; PinSocket_1x03_P2.54mm_Vertical
J2, J3, J4: Conn_02x08_Odd_Even; PinSocket_2x08_P2.54mm_Vertical
R1, R3: 0; R_0805_2012Metric_Pad1.20x1.40mm_HandSolder
R2: 50; R_0805_2012Metric_Pad1.20x1.40mm_HandSolder
U1: ESP32-DevKit-C; ESP32-devkitC-v4
U2: LM7805_TO220; TO-220-3_Vertical
U3: MCP1754S-3302xCB; SOT-23
U4: MCP1825S-3.3V; SOT-223-3_TabPin2
U5: MCP1501-33xSN; SOIC-8_3.9x4.9mm_P1.27mm
U6, U7: MCP3464R; TSSOP-20_4.4x6.5mm_P0.65mm
U8: DAC8568IAPW; TSSOP-16-1EP_4.4x5mm_P0.65mm
X1: ECS-2520MVLC-049-BN-TR; Oscillator_SMD_ECS_2520MV-xxx-xx-4Pin_2.5x2.0mm

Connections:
+3.3VA: C6.1, C8.1, C16.1, C18.1, U3.2 (VO), U6.1 (AV_{DD}), U7.1 (AV_{DD})
+3.3VDAC: C13.1, R1.1, R2.1, U5.7 (OUT), U5.8 (FB), U6.4 (REFIN+), U7.4 (REFIN+)
+3V3: C7.1, C9.1, C11.1, C14.1, C15.1, C17.1, U4.3 (VO), U6.20 (DV_{DD}), U7.20 (DV_{DD}), U8.3 (AV_{DD}), X1.4 (VDD)
+5V: C2.1, C3.1, C4.1, C5.1, C10.1, U1.38 (5V), U2.3 (VO), U3.3 (VI), U4.1 (VI), U5.1 (VDD), U5.3 (~SHDN)
+12V: C1.1, J1.1, U2.1 (VI)
ADC1_1: J2.1, U6.5 (CH0)
ADC1_2: J2.3, U6.6 (CH1)
ADC1_3: J2.5, U6.7 (CH2)
ADC1_4: J2.7, U6.8 (CH3)
ADC1_5: J2.9, U6.9 (CH4)
ADC1_6: J2.11, U6.10 (CH5)
ADC1_7: J2.13, U6.11 (CH6)
ADC1_8: J2.15, U6.12 (CH7)
ADC2_1: J3.1, U7.5 (CH0)
ADC2_2: J3.3, U7.6 (CH1)
ADC2_3: J3.5, U7.7 (CH2)
ADC2_4: J3.7, U7.8 (CH3)
ADC2_5: J3.9, U7.9 (CH4)
ADC2_6: J3.11, U7.10 (CH5)
ADC2_7: J3.13, U7.11 (CH6)
ADC2_8: J3.15, U7.12 (CH7)
CLK: R3.2, U6.18 (MLCK), U7.18 (MLCK)
Earth: C1.2, C2.2, C3.2, C4.2, C5.2, C6.2, C7.2, C8.2, C9.2, C10.2, C11.2, C12.2, C13.2, C14.2, C15.2, C16.2, C17.2, C18.2, J1.2, J1.3, J2.2, J2.4, J2.6, J2.8, J2.10, J2.12, J2.14, J2.16, J3.2, J3.4, J3.6, J3.8, J3.10, J3.12, J3.14, J3.16, J4.2, J4.4, J4.6, J4.8, J4.10, J4.12, J4.14, J4.16, U1.13 (GND), U1.19 (GND), U1.33 (GND), U2.2 (GND), U3.1 (GND), U4.2 (GND), U5.2 (GND), U5.4 (GND), U5.5 (GND), U5.6 (GND), U6.2 (A_{GND}), U6.3 (REFIN-), U6.19 (D_{GND}), U7.2 (A_{GND}), U7.3 (REFIN-), U7.19 (D_{GND}), U8.14 (GND), X1.2 (GND)
LDAC: U1.8 (16), U8.1 (LDAC)
MDAT: U1.25 (35), U6.17 (~IRQ/MDAT), U7.17 (~IRQ/MDAT)
unnamed: C12.1, R2.2
unnamed: R1.2, U8.8 (V_{REF}IN)
unnamed: R3.1, X1.3 (OUT)
SI: U1.32 (12), U6.15 (SDI), U7.15 (SDI)
SK: U1.31 (14), U6.14 (SCK), U7.14 (SCK), U8.16 (SCLK)
SO: U1.34 (13), U6.16 (SDO), U7.16 (SDO), U8.15 (D_{IN})
VoutA: J4.15, U8.4 (V_{OUT}A)
VoutB: J4.1, U8.13 (V_{OUT}B)
VoutC: J4.13, U8.5 (V_{OUT}C)
VoutD: J4.3, U8.12 (V_{OUT}D)
VoutE: J4.11, U8.6 (V_{OUT}E)
VoutF: J4.5, U8.11 (V_{OUT}F)
VoutG: J4.9, U8.7 (V_{OUT}G)
VoutH: J4.7, U8.10 (V_{OUT}H)
~ADC1_CS: U1.27 (33), U6.13 (~CS)
~ADC2_CS: U1.26 (32), U7.13 (~CS)
~CLR: U1.9 (17), U8.9 (~CLR)
~DAC_CS: U1.30 (27), U8.2 (~SYNC)
